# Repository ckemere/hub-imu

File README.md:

# USB IMU for camera rigs

Small KiCad 9 boards that add a Bosch BNO055 9-axis IMU to a pair of USB cameras mounted on a 3/4" webbing strap.

| Folder | Board | Status |
|---|---|---|
| [`hub_imu/`](hub_imu/) | **hub_imu** ("EweFeel 1.0"): 21 x 14.4 mm module. An STM32F042 bridges USB to the BNO055 over I2C. It stacks onto a hub through a 1x4 2.54 mm header. | Built and working |
| [`hub_cam/`](hub_cam/) | **hub_cam**: FE1.1S 4-port USB 2.0 high-speed hub carrier, about 16.5 x 23 mm. It has two JST-GH crimp connectors for the cameras, solder holes for the host cable, and a header that the hub_imu module stacks onto. | Schematic drafted, layout not started |

## Why hub_cam

hub_imu was first stacked onto an off-the-shelf FE1.1S hub board ([Amazon](https://www.amazon.com/dp/B0GTVPVPV9)). That hub has two problems:

- Its port holes are on a 2.0 mm pitch, so they don't line up with hub_imu's 2.54 mm header.
- The camera wires have to be soldered to it, and their insulation melts easily.

hub_cam replaces that hub with one sized to the strap. The cameras plug in through crimped JST-GH connectors, and the existing hub_imu modules stack directly on top.

## License

All hardware in this repository is licensed under the [CERN Open Hardware Licence v2, Permissive](LICENSE) (CERN-OHL-P-2.0).

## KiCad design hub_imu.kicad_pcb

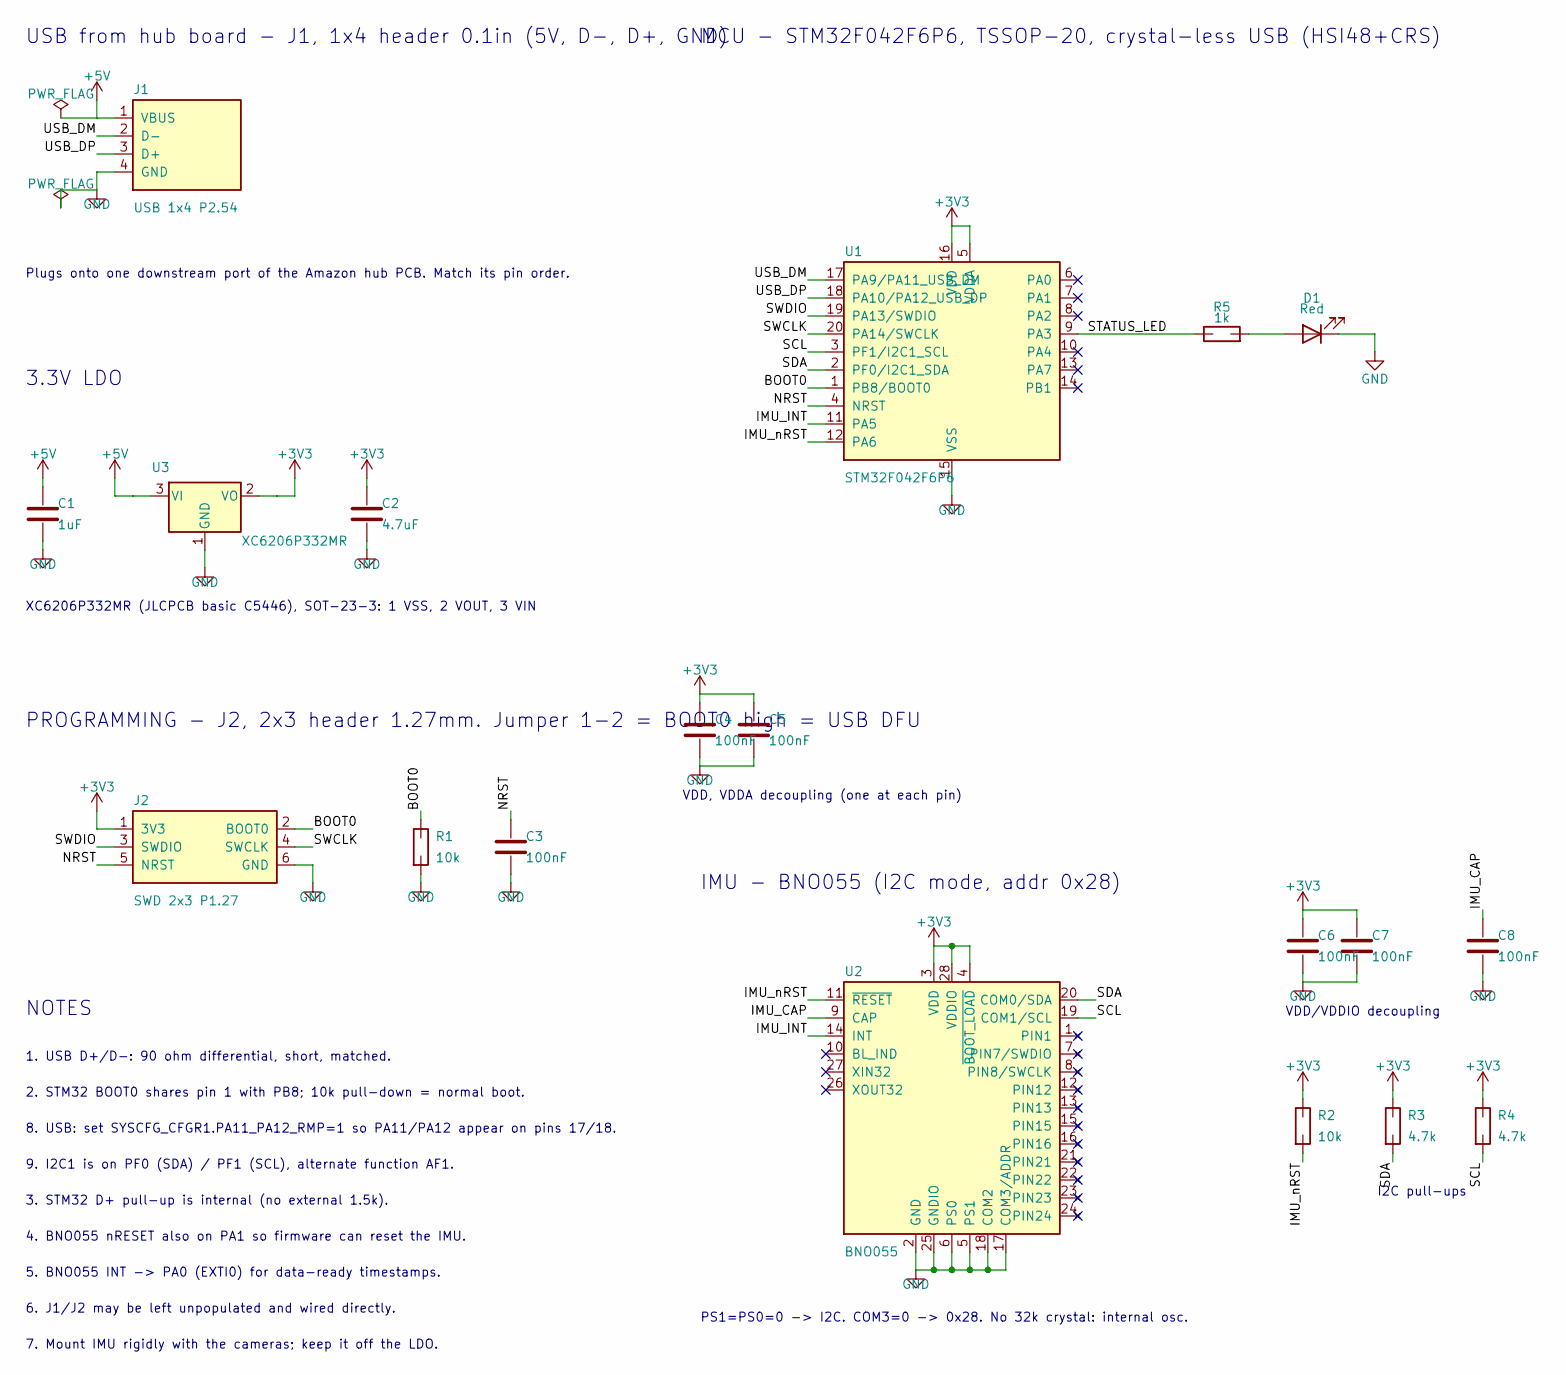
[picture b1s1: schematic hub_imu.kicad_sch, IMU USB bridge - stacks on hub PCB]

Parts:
C1: 1uF; C_0402_1005Metric; JLCPCB Part # C52923
C2: 4.7uF; C_0402_1005Metric; JLCPCB Part # C23733
C3, C4, C5, C6, C7, C8: 100nF; C_0402_1005Metric; JLCPCB Part # C1525
D1: Red; LED_0603_1608Metric; JLCPCB Part # C2286
J1: USB 1x4 P2.54; PinHeader_1x04_P2.54mm_Vertical
J2: SWD 2x3 P1.27; PinHeader_2x03_P1.27mm_Vertical
R1, R2: 10k; R_0402_1005Metric; JLCPCB Part # C25744
R3, R4: 4.7k; R_0402_1005Metric; JLCPCB Part # C25900
R5: 1k; R_0402_1005Metric; JLCPCB Part # C11702
U1: STM32F042F6P6; TSSOP-20_4.4x6.5mm_P0.65mm
U2: BNO055; LGA-28_5.2x3.8mm_P0.5mm
U3: XC6206P332MR; SOT-23-3; JLCPCB Part # C5446

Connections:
+3V3: C2.1, C4.1, C5.1, C6.1, C7.1, J2.1 (3V3), R2.1, R3.1, R4.1, U1.5 (VDDA), U1.16 (VDD), U2.3 (VDD), U2.4 (~BOOT_LOAD), U2.28 (VDDIO), U3.2 (VO)
+5V: C1.1, J1.1 (VBUS), U3.3 (VI)
/BOOT0: J2.2 (BOOT0), R1.1, U1.1 (PB8/BOOT0)
/IMU_CAP: C8.1, U2.9 (CAP)
/IMU_INT: U1.11 (PA5), U2.14 (INT)
/IMU_nRST: R2.2, U1.12 (PA6), U2.11 (~RESET)
/NRST: C3.1, J2.5 (NRST), U1.4 (NRST)
/SCL: R4.2, U1.3 (PF1/I2C1_SCL), U2.19 (COM1/SCL)
/SDA: R3.2, U1.2 (PF0/I2C1_SDA), U2.20 (COM0/SDA)
/STATUS_LED: R5.1, U1.9 (PA3)
/SWCLK: J2.4 (SWCLK), U1.20 (PA14/SWCLK)
/SWDIO: J2.3 (SWDIO), U1.19 (PA13/SWDIO)
/USB_DM: J1.2 (D-), U1.17 (PA9/PA11_USB_DM)
/USB_DP: J1.3 (D+), U1.18 (PA10/PA12_USB_DP)
GND: C1.2, C2.2, C3.2, C4.2, C5.2, C6.2, C7.2, C8.2, D1.1 (K), J1.4 (GND), J2.6 (GND), R1.2, U1.15 (VSS), U2.2 (GND), U2.5 (PS1), U2.6 (PS0), U2.17 (COM3/ADDR), U2.18 (COM2), U2.25 (GNDIO), U3.1 (GND)
unnamed: D1.2 (A), R5.2

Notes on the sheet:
3. STM32 D+ pull-up is internal (no external 1.5k).
Plugs onto one downstream port of the Amazon hub PCB. Match its pin order.
IMU - BNO055 (I2C mode, addr 0x28)
8. USB: set SYSCFG_CFGR1.PA11_PA12_RMP=1 so PA11/PA12 appear on pins 17/18.
PROGRAMMING - J2, 2x3 header 1.27mm. Jumper 1-2 = BOOT0 high = USB DFU
7. Mount IMU rigidly with the cameras; keep it off the LDO.
9. I2C1 is on PF0 (SDA) / PF1 (SCL), alternate function AF1.
I2C pull-ups
USB from hub board - J1, 1x4 header 0.1in (5V, D-, D+, GND)
VDD, VDDA decoupling (one at each pin)
PS1=PS0=0 -> I2C. COM3=0 -> 0x28. No 32k crystal: internal osc.
5. BNO055 INT -> PA0 (EXTI0) for data-ready timestamps.
1. USB D+/D-: 90 ohm differential, short, matched.
6. J1/J2 may be left unpopulated and wired directly.
NOTES
VDD/VDDIO decoupling
MCU - STM32F042F6P6, TSSOP-20, crystal-less USB (HSI48+CRS)
3.3V LDO
XC6206P332MR (JLCPCB basic C5446), SOT-23-3: 1 VSS, 2 VOUT, 3 VIN
4. BNO055 nRESET also on PA1 so firmware can reset the IMU.
2. STM32 BOOT0 shares pin 1 with PB8; 10k pull-down = normal boot.

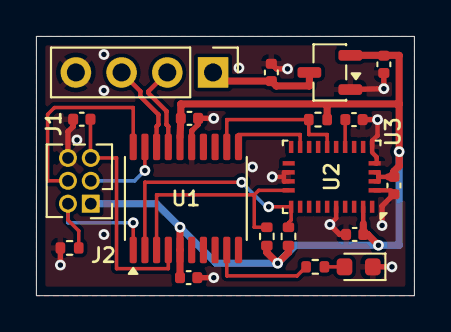
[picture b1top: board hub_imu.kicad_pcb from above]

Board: 2 copper layers, 21.0 x 14.4 mm, 19 parts (0 on the bottom side), 16 nets.
